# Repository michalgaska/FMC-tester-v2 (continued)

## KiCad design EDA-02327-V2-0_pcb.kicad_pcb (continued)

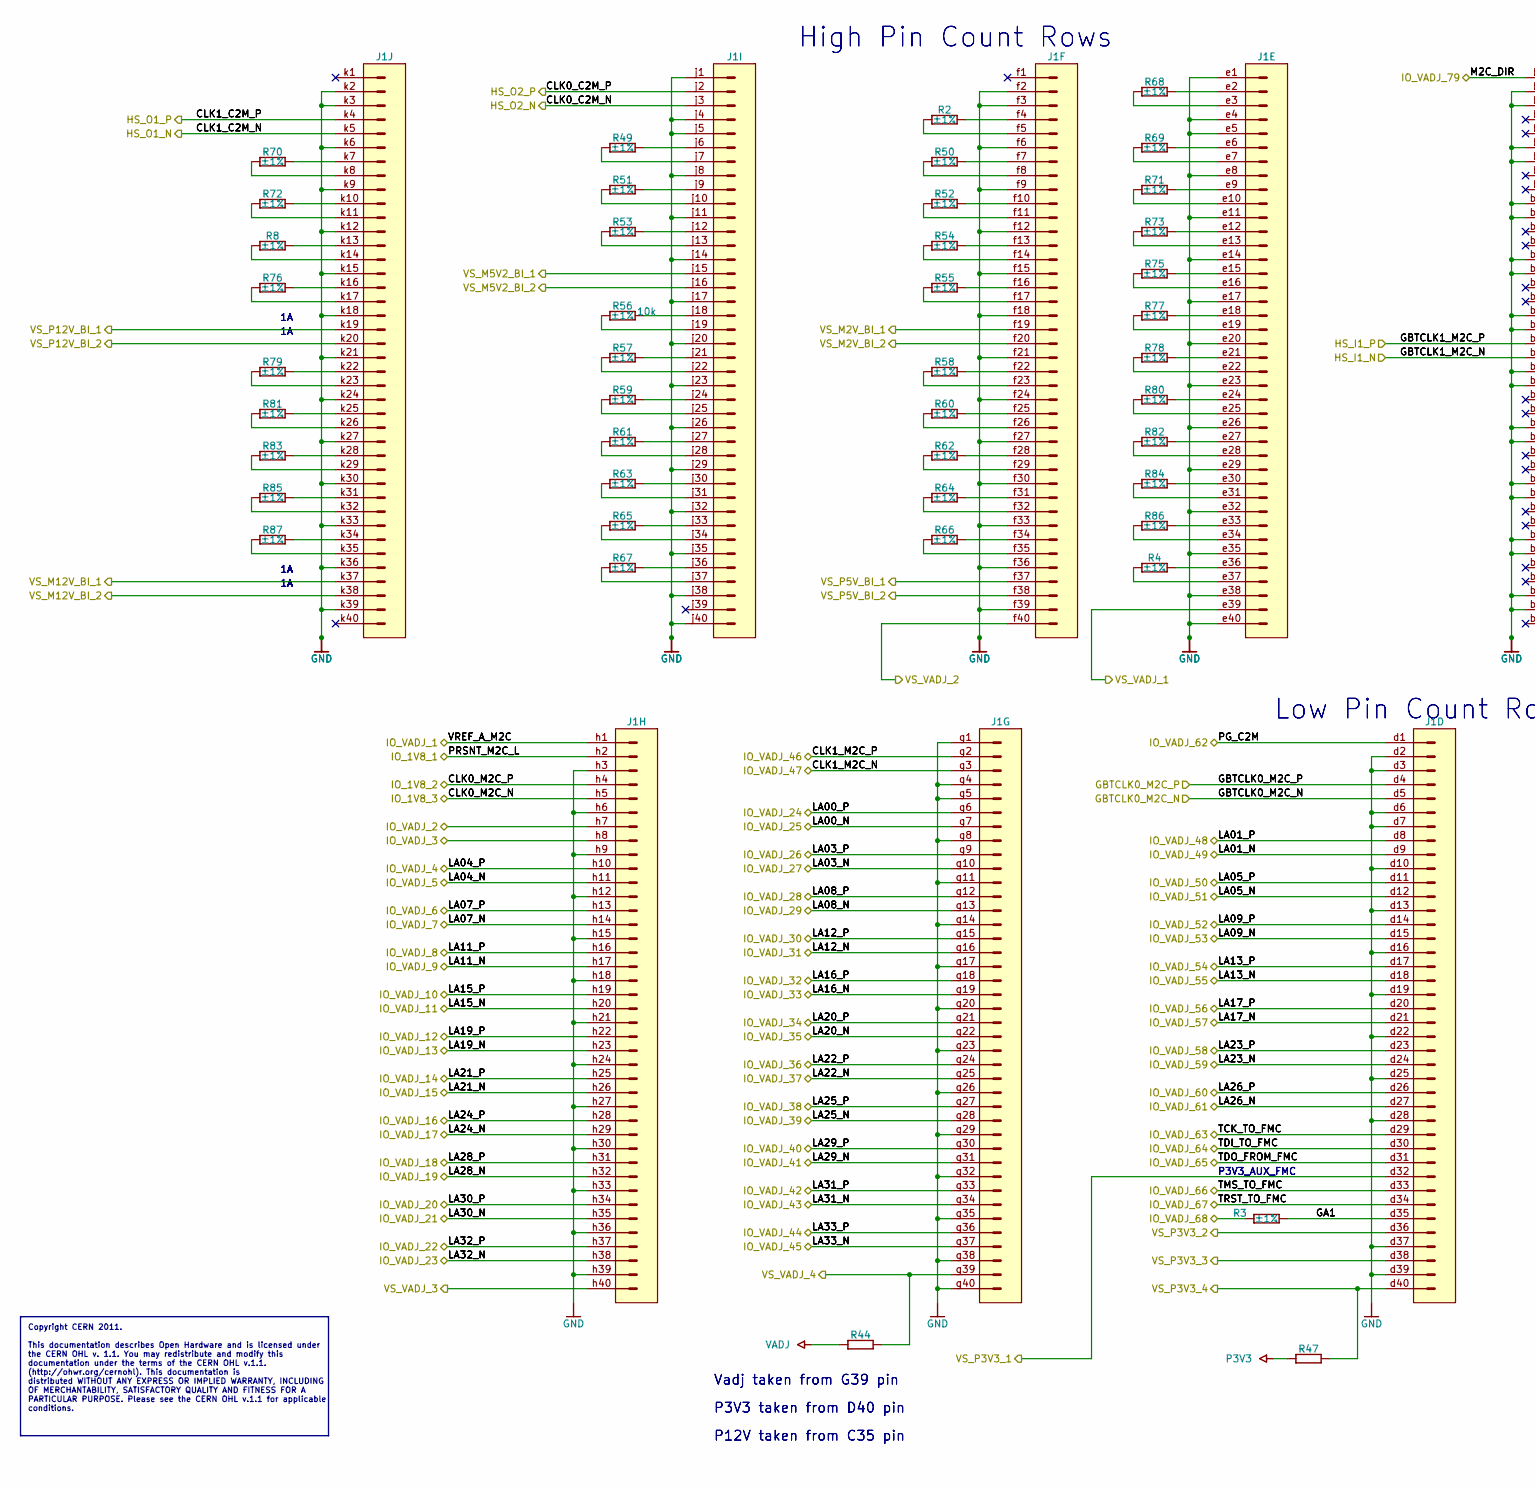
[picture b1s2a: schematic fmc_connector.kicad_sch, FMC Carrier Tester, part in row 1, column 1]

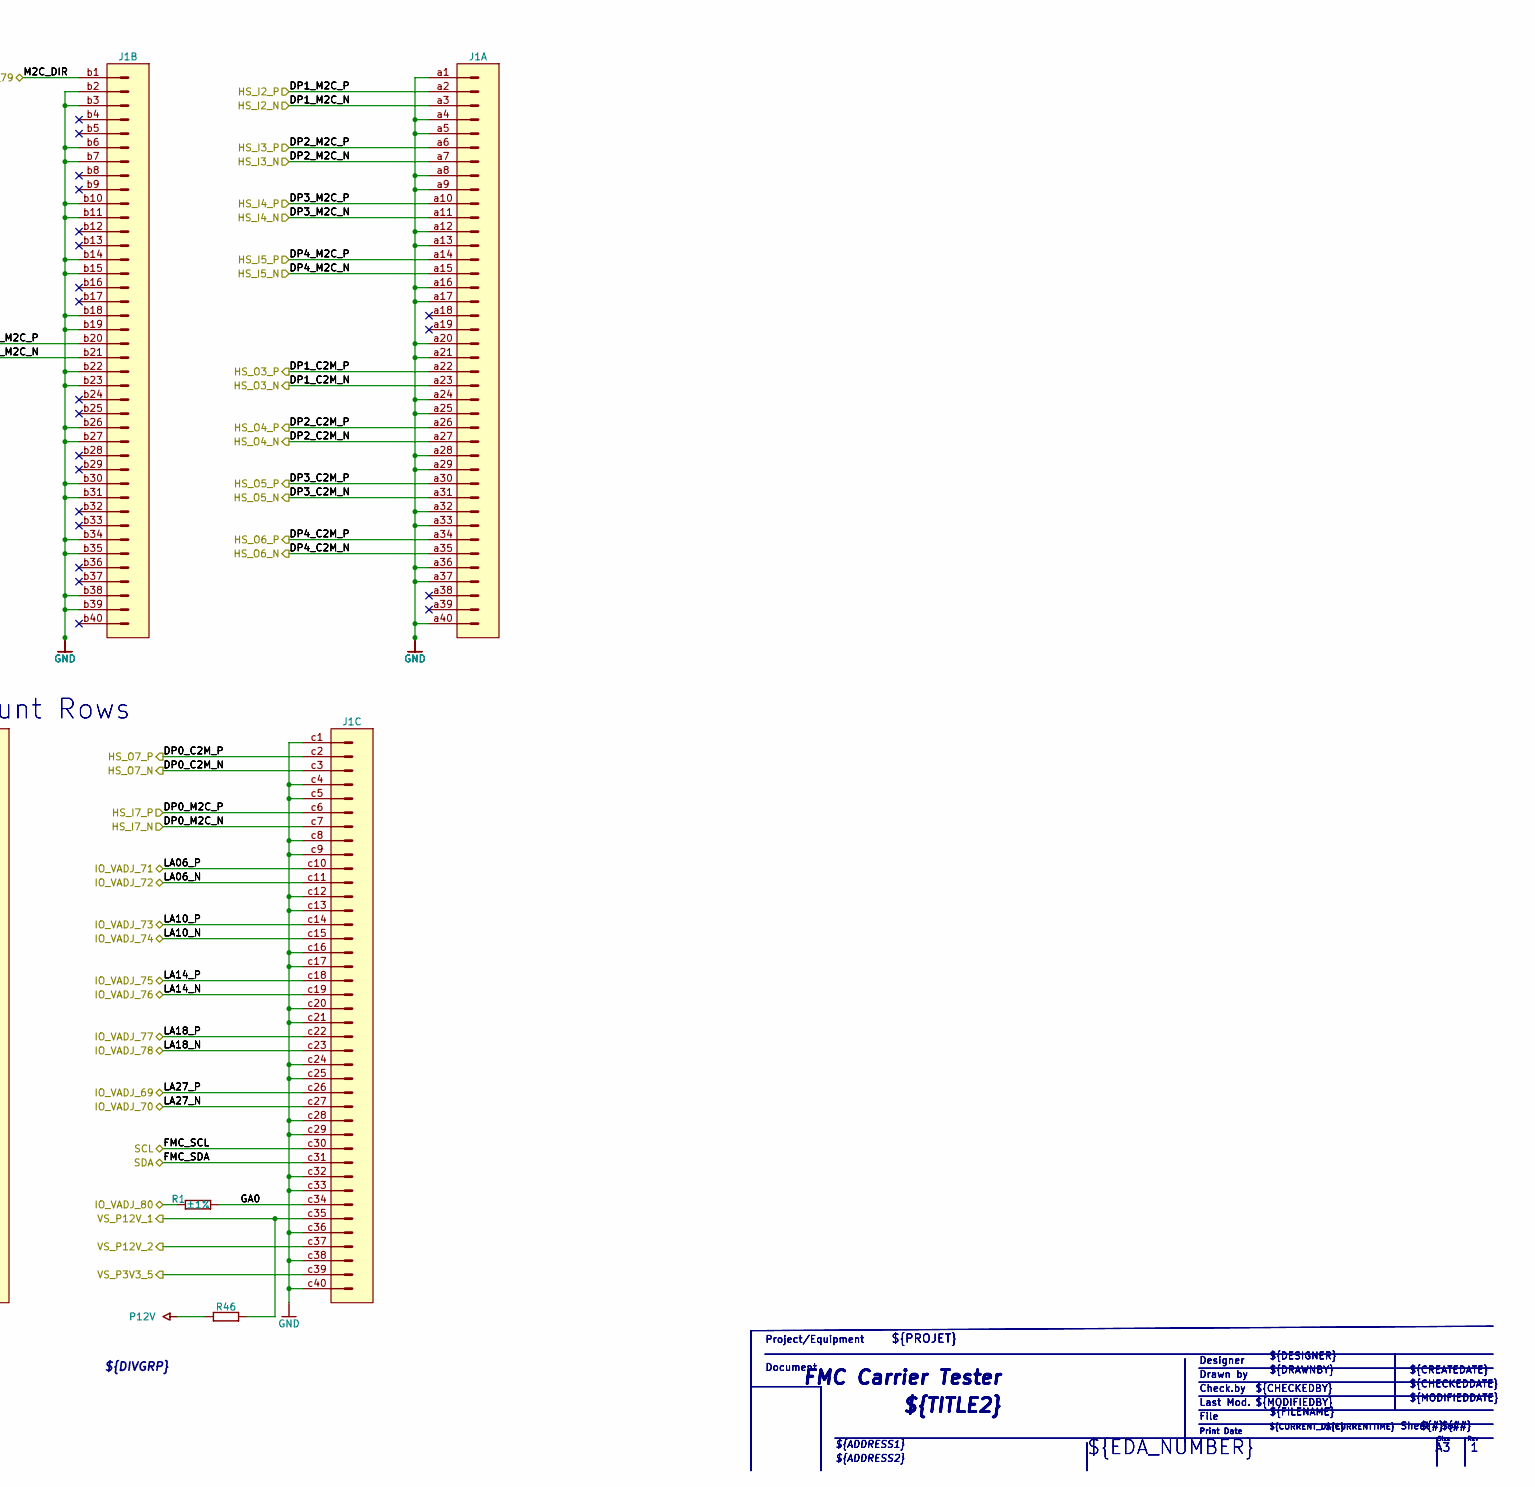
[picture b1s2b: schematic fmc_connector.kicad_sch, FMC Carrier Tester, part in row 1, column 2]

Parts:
J1: SAMTEC_ASP-134488-01; PART NUMBER SAMTEC_ASP-134488-01
R1, R2, R3, R4, R8, R49, R50, R51, R52, R53, R54, R55, R56, R57, R58, R59, R60, R61, R62, R63, R64, R65, R66, R67, R68, R69, R70, R71, R72, R73, R75, R76, R77, R78, R79, R80, R81, R82, R83, R84, R85, R86, R87: RESC1005X40N; TOLERANCE ±1%; PART NUMBER R0402_10K_1%_0.0625W_100PPM
R44, R46, R47: RESC1608X55N; PART NUMBER R0603_0R_JUMPER

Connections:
/HS_I1_N: J1.b21; also elsewhere on the board
/HS_I1_P: J1.b20; also elsewhere on the board
/HS_I2_N: J1.a3; also elsewhere on the board
/HS_I2_P: J1.a2; also elsewhere on the board
/HS_I3_N: J1.a7; also elsewhere on the board
/HS_I3_P: J1.a6; also elsewhere on the board
/HS_I4_N: J1.a11; also elsewhere on the board
/HS_I4_P: J1.a10; also elsewhere on the board
/HS_I5_N: J1.a15; also elsewhere on the board
/HS_I5_P: J1.a14; also elsewhere on the board
/HS_I7_N: J1.c7; also elsewhere on the board
/HS_I7_P: J1.c6; also elsewhere on the board
/HS_O1_N: J1.k5; also elsewhere on the board
/HS_O1_P: J1.k4; also elsewhere on the board
/HS_O2_N: J1.j3; also elsewhere on the board
/HS_O2_P: J1.j2; also elsewhere on the board
/HS_O3_N: J1.a23; also elsewhere on the board
/HS_O3_P: J1.a22; also elsewhere on the board
/HS_O4_N: J1.a27; also elsewhere on the board
/HS_O4_P: J1.a26; also elsewhere on the board
/HS_O5_N: J1.a31; also elsewhere on the board
/HS_O5_P: J1.a30; also elsewhere on the board
/HS_O6_N: J1.a35; also elsewhere on the board
/HS_O6_P: J1.a34; also elsewhere on the board
/HS_O7_N: J1.c3; also elsewhere on the board
/HS_O7_P: J1.c2; also elsewhere on the board
/IO_1V8_1: J1.h2; also elsewhere on the board
/IO_1V8_2: J1.h4; also elsewhere on the board
/IO_1V8_3: J1.h5; also elsewhere on the board
/IO_VADJ_1: J1.h1; also elsewhere on the board
/IO_VADJ_4: J1.h10; also elsewhere on the board
/IO_VADJ_5: J1.h11; also elsewhere on the board
/IO_VADJ_6: J1.h13; also elsewhere on the board
/IO_VADJ_7: J1.h14; also elsewhere on the board
/IO_VADJ_8: J1.h16; also elsewhere on the board
/IO_VADJ_9: J1.h17; also elsewhere on the board
/IO_VADJ_10: J1.h19; also elsewhere on the board
/IO_VADJ_11: J1.h20; also elsewhere on the board
/IO_VADJ_12: J1.h22; also elsewhere on the board
/IO_VADJ_13: J1.h23; also elsewhere on the board
/IO_VADJ_14: J1.h25; also elsewhere on the board
/IO_VADJ_15: J1.h26; also elsewhere on the board
/IO_VADJ_16: J1.h28; also elsewhere on the board
/IO_VADJ_17: J1.h29; also elsewhere on the board
/IO_VADJ_18: J1.h31; also elsewhere on the board
/IO_VADJ_19: J1.h32; also elsewhere on the board
/IO_VADJ_20: J1.h34; also elsewhere on the board
/IO_VADJ_21: J1.h35; also elsewhere on the board
/IO_VADJ_22: J1.h37; also elsewhere on the board
/IO_VADJ_23: J1.h38; also elsewhere on the board
/IO_VADJ_24: J1.g6; also elsewhere on the board
/IO_VADJ_25: J1.g7; also elsewhere on the board
/IO_VADJ_26: J1.g9; also elsewhere on the board
/IO_VADJ_27: J1.g10; also elsewhere on the board
/IO_VADJ_28: J1.g12; also elsewhere on the board
/IO_VADJ_29: J1.g13; also elsewhere on the board
/IO_VADJ_30: J1.g15; also elsewhere on the board
/IO_VADJ_31: J1.g16; also elsewhere on the board
/IO_VADJ_32: J1.g18; also elsewhere on the board
/IO_VADJ_33: J1.g19; also elsewhere on the board
/IO_VADJ_34: J1.g21; also elsewhere on the board
/IO_VADJ_35: J1.g22; also elsewhere on the board
/IO_VADJ_36: J1.g24; also elsewhere on the board
/IO_VADJ_37: J1.g25; also elsewhere on the board
/IO_VADJ_38: J1.g27; also elsewhere on the board
/IO_VADJ_39: J1.g28; also elsewhere on the board
/IO_VADJ_40: J1.g30; also elsewhere on the board
/IO_VADJ_41: J1.g31; also elsewhere on the board
/IO_VADJ_42: J1.g33; also elsewhere on the board
/IO_VADJ_43: J1.g34; also elsewhere on the board
/IO_VADJ_44: J1.g36; also elsewhere on the board
/IO_VADJ_45: J1.g37; also elsewhere on the board
/IO_VADJ_46: J1.g2; also elsewhere on the board
/IO_VADJ_47: J1.g3; also elsewhere on the board
/IO_VADJ_48: J1.d8; also elsewhere on the board
/IO_VADJ_49: J1.d9; also elsewhere on the board
/IO_VADJ_50: J1.d11; also elsewhere on the board
/IO_VADJ_51: J1.d12; also elsewhere on the board
/IO_VADJ_52: J1.d14; also elsewhere on the board
/IO_VADJ_53: J1.d15; also elsewhere on the board
/IO_VADJ_54: J1.d17; also elsewhere on the board
/IO_VADJ_55: J1.d18; also elsewhere on the board
/IO_VADJ_56: J1.d20; also elsewhere on the board
/IO_VADJ_57: J1.d21; also elsewhere on the board
/IO_VADJ_58: J1.d23; also elsewhere on the board
/IO_VADJ_59: J1.d24; also elsewhere on the board
/IO_VADJ_60: J1.d26; also elsewhere on the board
/IO_VADJ_61: J1.d27; also elsewhere on the board
/IO_VADJ_62: J1.d1; also elsewhere on the board
/IO_VADJ_63: J1.d29; also elsewhere on the board
/IO_VADJ_64: J1.d30; also elsewhere on the board
/IO_VADJ_65: J1.d31; also elsewhere on the board
/IO_VADJ_66: J1.d33; also elsewhere on the board
/IO_VADJ_67: J1.d34; also elsewhere on the board
/IO_VADJ_68: R3.1; also elsewhere on the board
/IO_VADJ_69: J1.c26; also elsewhere on the board
/IO_VADJ_70: J1.c27; also elsewhere on the board
/IO_VADJ_71: J1.c10; also elsewhere on the board
/IO_VADJ_72: J1.c11; also elsewhere on the board
/IO_VADJ_73: J1.c14; also elsewhere on the board
/IO_VADJ_74: J1.c15; also elsewhere on the board
/IO_VADJ_75: J1.c18; also elsewhere on the board
/IO_VADJ_76: J1.c19; also elsewhere on the board
/IO_VADJ_77: J1.c22; also elsewhere on the board
/IO_VADJ_78: J1.c23; also elsewhere on the board
/IO_VADJ_79: J1.b1; also elsewhere on the board
/IO_VADJ_80: R1.1; also elsewhere on the board
/SCL: J1.c30; also elsewhere on the board
/SCL_VADJ: J1.h7; also elsewhere on the board
/SDA: J1.c31; also elsewhere on the board
/SDA_VADJ: J1.h8; also elsewhere on the board
/U_fmc_connector/GA1: J1.d35, R3.2
/U_fmc_connector/GBTCLK0_M2C_N: J1.d5; also elsewhere on the board
/U_fmc_connector/GBTCLK0_M2C_P: J1.d4; also elsewhere on the board
/U_fmc_connector/VS_M2V_BI_1: J1.f19; also elsewhere on the board
/U_fmc_connector/VS_M2V_BI_2: J1.f20; also elsewhere on the board
/U_fmc_connector/VS_M5V2_BI_1: J1.j15; also elsewhere on the board
/U_fmc_connector/VS_M5V2_BI_2: J1.j16; also elsewhere on the board
/U_fmc_connector/VS_M12V_BI_1: J1.k37; also elsewhere on the board
/U_fmc_connector/VS_M12V_BI_2: J1.k38; also elsewhere on the board
/U_fmc_connector/VS_P3V3_1: J1.d32; also elsewhere on the board
/U_fmc_connector/VS_P3V3_2: J1.d36; also elsewhere on the board
/U_fmc_connector/VS_P3V3_3: J1.d38; also elsewhere on the board
/U_fmc_connector/VS_P3V3_4: J1.d40, R47.2; also elsewhere on the board
/U_fmc_connector/VS_P3V3_5: J1.c39; also elsewhere on the board
/U_fmc_connector/VS_P5V_BI_1: J1.f37; also elsewhere on the board
/U_fmc_connector/VS_P5V_BI_2: J1.f38; also elsewhere on the board
/U_fmc_connector/VS_P12V_1: J1.c35, R46.2; also elsewhere on the board
/U_fmc_connector/VS_P12V_2: J1.c37; also elsewhere on the board
/U_fmc_connector/VS_P12V_BI_1: J1.k19; also elsewhere on the board
/U_fmc_connector/VS_P12V_BI_2: J1.k20; also elsewhere on the board
/U_fmc_connector/VS_VADJ_1: J1.e39; also elsewhere on the board
/U_fmc_connector/VS_VADJ_2: J1.f40; also elsewhere on the board
/U_fmc_connector/VS_VADJ_3: J1.h40; also elsewhere on the board
/U_fmc_connector/VS_VADJ_4: J1.g39, R44.2; also elsewhere on the board
GND: J1.a1, J1.a4, J1.a5, J1.a8, J1.a9, J1.a12, J1.a13, J1.a16, J1.a17, J1.a20, J1.a21, J1.a24, J1.a25, J1.a28, J1.a29, J1.a32, J1.a33, J1.a36, J1.a37, J1.a40, J1.b2, J1.b3, J1.b6, J1.b7, J1.b10, J1.b11, J1.b14, J1.b15, J1.b18, J1.b19, J1.b22, J1.b23, J1.b26, J1.b27, J1.b30, J1.b31, J1.b34, J1.b35, J1.b38, J1.b39, J1.c1, J1.c4, J1.c5, J1.c8, J1.c9, J1.c12, J1.c13, J1.c16, J1.c17, J1.c20, J1.c21, J1.c24, J1.c25, J1.c28, J1.c29, J1.c32, J1.c33, J1.c36, J1.c38, J1.c40, J1.d2, J1.d3, J1.d6, J1.d7, J1.d10, J1.d13, J1.d16, J1.d19, J1.d22, J1.d25, J1.d28, J1.d37, J1.d39, J1.e1, J1.e4, J1.e5, J1.e8, J1.e11, J1.e14, J1.e17, J1.e20, J1.e23, J1.e26, J1.e29, J1.e32, J1.e35, J1.e38, J1.e40, J1.f2, J1.f3, J1.f6, J1.f9, J1.f12, J1.f15, J1.f18, J1.f21, J1.f24, J1.f27, J1.f30, J1.f33, J1.f36, J1.f39, J1.g1, J1.g4, J1.g5, J1.g8, J1.g11, J1.g14, J1.g17, J1.g20, J1.g23, J1.g26, J1.g29, J1.g32, J1.g35, J1.g38, J1.g40, J1.h3, J1.h6, J1.h9, J1.h12, J1.h15, J1.h18, J1.h21, J1.h24, J1.h27, J1.h30, J1.h33, J1.h36, J1.h39, J1.j1, J1.j4, J1.j5, J1.j8, J1.j11, J1.j14, J1.j17, J1.j20, J1.j23, J1.j26, J1.j29, J1.j32, J1.j35, J1.j38, J1.j40, J1.k2, J1.k3, J1.k6, J1.k9, J1.k12, J1.k15, J1.k18, J1.k21, J1.k24, J1.k27, J1.k30, J1.k33, J1.k36, J1.k39; also elsewhere on the board
unnamed: J1.c34, R1.2
unnamed: J1.e9, R71.2
unnamed: J1.e10, R71.1
unnamed: J1.e12, R73.2
unnamed: J1.e13, R73.1
unnamed: J1.e24, R80.2
unnamed: J1.e25, R80.1
unnamed: J1.e27, R82.2
unnamed: J1.e28, R82.1
unnamed: J1.j6, R49.2
unnamed: J1.j30, R63.2
unnamed: J1.j31, R63.1
unnamed: J1.j33, R65.2
unnamed: J1.j34, R65.1
unnamed: J1.j36, R67.2
unnamed: J1.j37, R67.1
unnamed: J1.k14, R8.1
unnamed: J1.k16, R76.2
unnamed: J1.k17, R76.1
unnamed: J1.k22, R79.2
unnamed: J1.k23, R79.1
unnamed: J1.k25, R81.2
unnamed: J1.k26, R81.1
unnamed: J1.k28, R83.2
unnamed: J1.k29, R83.1
unnamed: J1.k31, R85.2
unnamed: J1.k32, R85.1
unnamed: J1.k34, R87.2
unnamed: J1.k35, R87.1
unnamed: J1.f5, R2.1
unnamed: J1.f4, R2.2
unnamed: J1.e37, R4.1
unnamed: J1.e36, R4.2
unnamed: J1.k13, R8.2
unnamed: J1.j7, R49.1
unnamed: J1.f8, R50.1
unnamed: J1.f7, R50.2
unnamed: J1.j10, R51.1
unnamed: J1.j9, R51.2
unnamed: J1.f11, R52.1
unnamed: J1.f10, R52.2
unnamed: J1.j13, R53.1
unnamed: J1.j12, R53.2
unnamed: J1.f14, R54.1
unnamed: J1.f13, R54.2
unnamed: J1.f17, R55.1
unnamed: J1.f16, R55.2
unnamed: J1.j19, R56.1
unnamed: J1.j18, R56.2
unnamed: J1.j22, R57.1
unnamed: J1.j21, R57.2
unnamed: J1.f23, R58.1
unnamed: J1.f22, R58.2
unnamed: J1.j25, R59.1
unnamed: J1.j24, R59.2
unnamed: J1.f26, R60.1
unnamed: J1.f25, R60.2
unnamed: J1.j28, R61.1
unnamed: J1.j27, R61.2
unnamed: J1.f29, R62.1
unnamed: J1.f28, R62.2
unnamed: J1.f32, R64.1
unnamed: J1.f31, R64.2
unnamed: J1.f35, R66.1
unnamed: J1.f34, R66.2
unnamed: J1.e3, R68.1
unnamed: J1.e2, R68.2
unnamed: J1.e7, R69.1
unnamed: J1.e6, R69.2
unnamed: J1.k8, R70.1
unnamed: J1.k7, R70.2
unnamed: J1.k11, R72.1
unnamed: J1.k10, R72.2
unnamed: J1.e16, R75.1
unnamed: J1.e15, R75.2
unnamed: J1.e19, R77.1
unnamed: J1.e18, R77.2
unnamed: J1.e22, R78.1
unnamed: J1.e21, R78.2
unnamed: J1.e31, R84.1
unnamed: J1.e30, R84.2
unnamed: J1.e34, R86.1
unnamed: J1.e33, R86.2
P3V3: R47.1; also elsewhere on the board
P12V: R46.1; also elsewhere on the board
VADJ: R44.1; also elsewhere on the board

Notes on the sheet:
Copyright CERN 2011. This documentation describes Open Hardware and is licensed under the CERN OHL v. 1.1. You may redistribute and modify this documentation under the terms of the CERN OHL v.1.1. (http://ohwr.org/cernohl). This documentation is distributed WITHOUT ANY EXPRESS OR IMPLIED WARRANTY, 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
${MODIFIEDBY}
Sheet
${CHECKEDDATE}
${CURRENTTIME}
Drawn by
P12V taken from C35 pin
Vadj taken from G39 pin
${PROJET}
${DRAWNBY}
File
Print Date
${CHECKEDBY}
High Pin Count Rows
Project/Equipment
Check.by
Document
Low Pin Count Rows
${REVISION}
${ADDRESS2}
${DIVGRP}
${CREATEDATE}
Last Mod.
${TITLE}
Size
P3V3_AUX_FMC
Designer
P3V3 taken from D40 pin
${FILENAME}
${TITLE2}
${ADDRESS1}
${#}
${DESIGNER}
${MODIFIEDDATE}
${##}
${CURRENT_DATE}
${EDA_NUMBER}
Rev

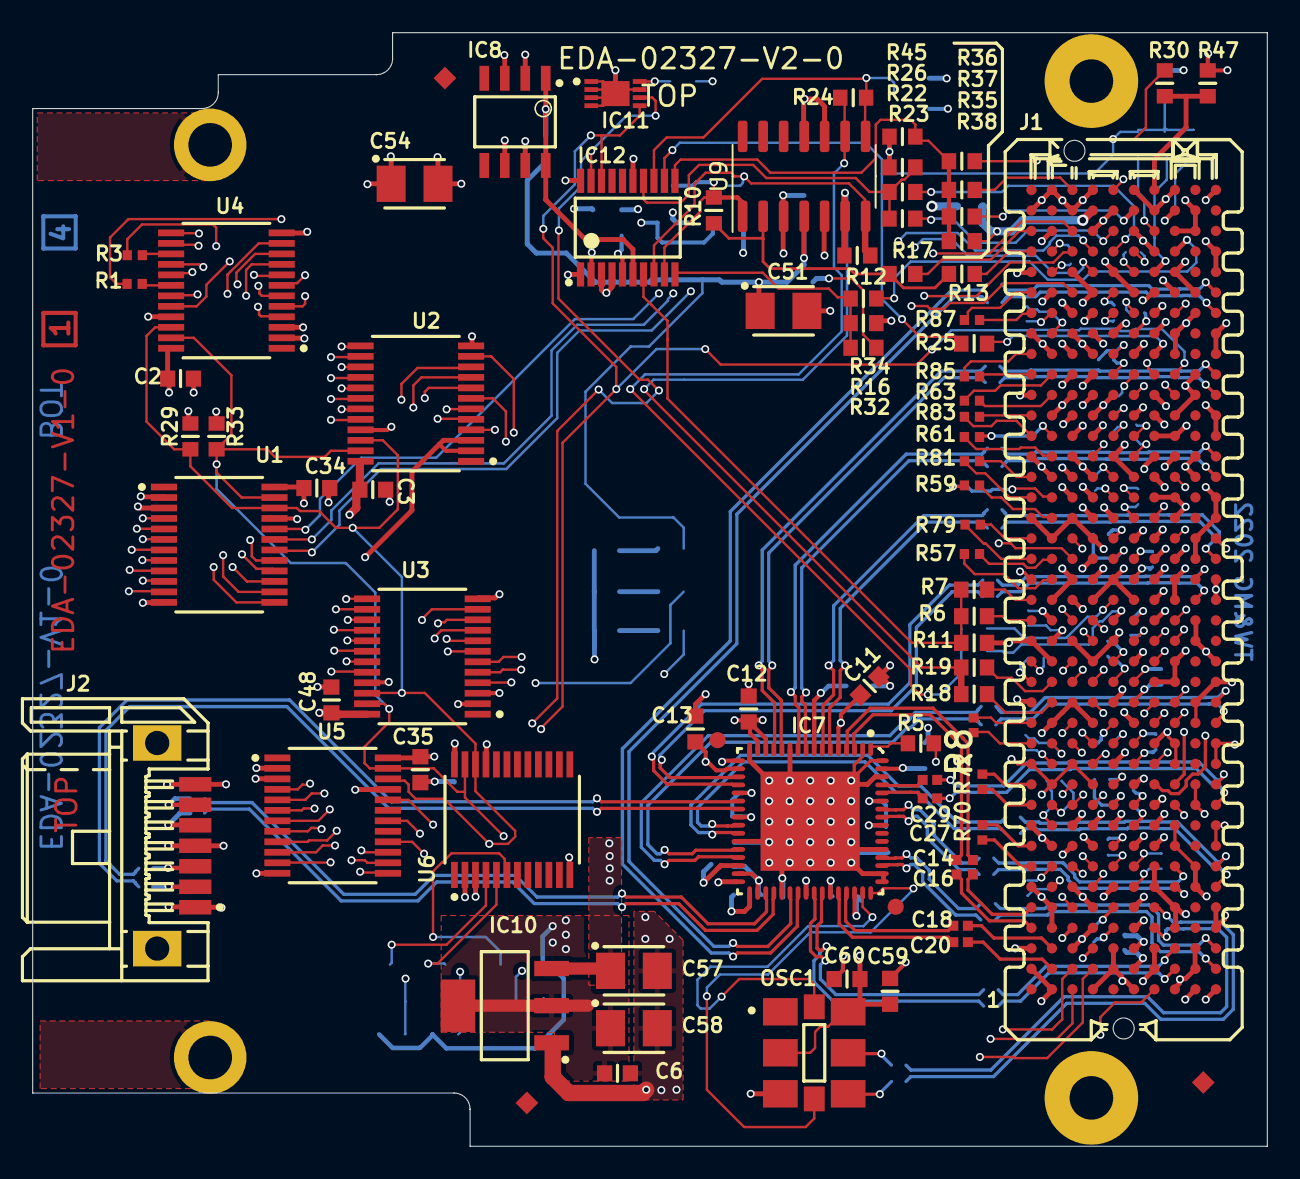
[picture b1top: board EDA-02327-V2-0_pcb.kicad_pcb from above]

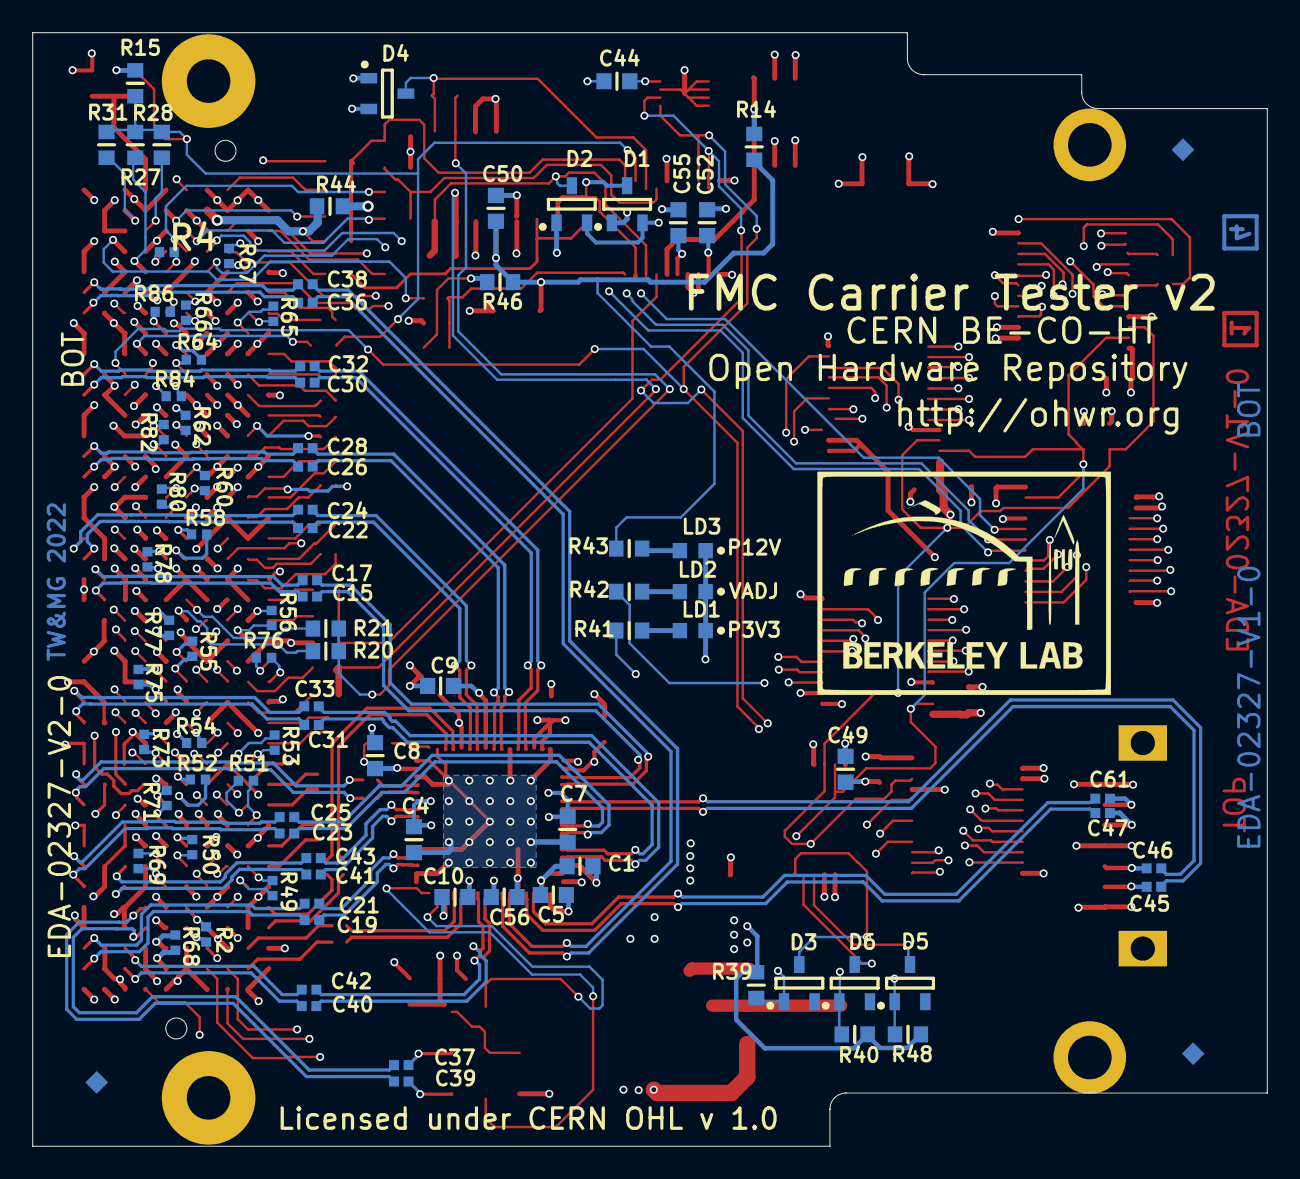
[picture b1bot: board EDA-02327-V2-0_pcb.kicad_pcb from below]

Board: 4 copper layers, 76.5 x 69.0 mm, 179 parts (95 on the bottom side), 278 nets.

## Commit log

2022-08-10 First
